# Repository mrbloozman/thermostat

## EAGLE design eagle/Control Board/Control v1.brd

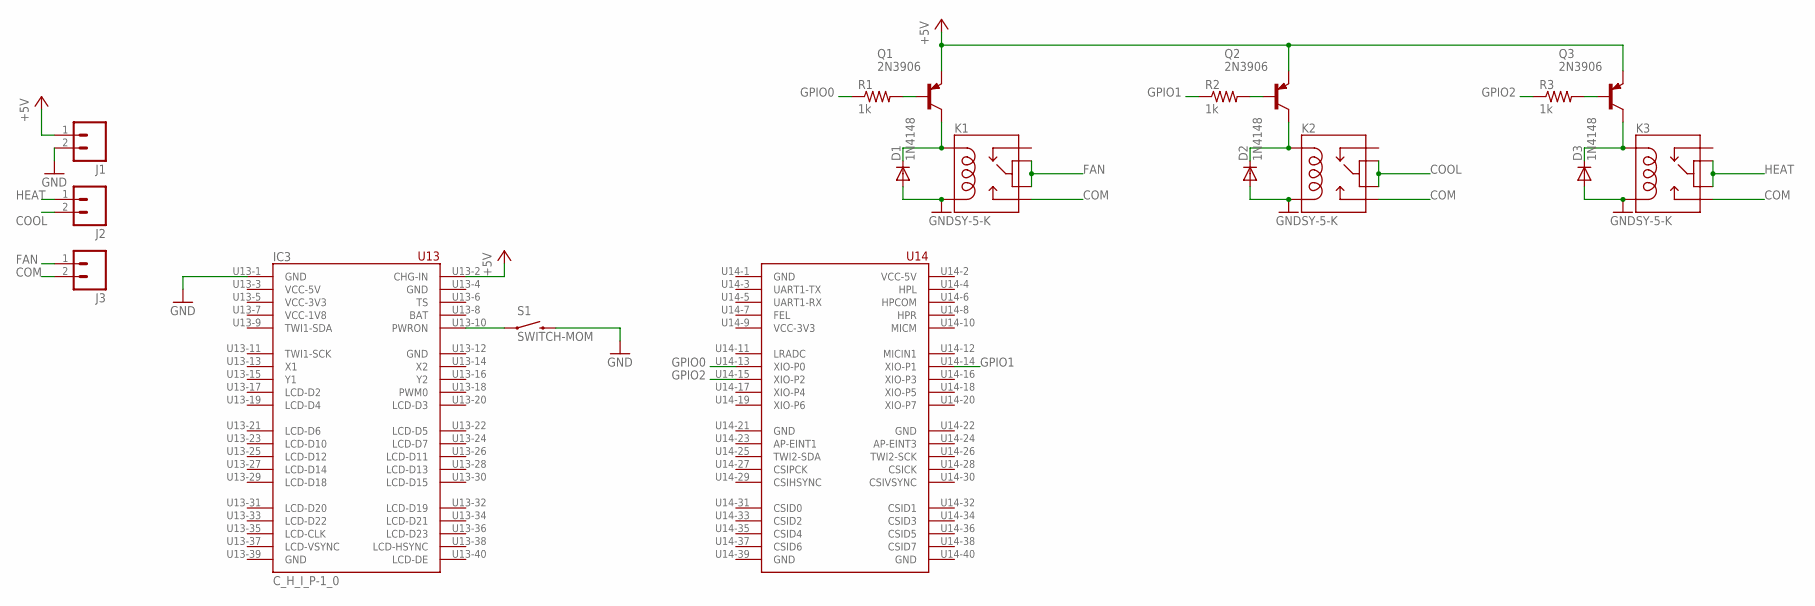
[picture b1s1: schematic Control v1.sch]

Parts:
D1, D2, D3: 1N4148; DO35-7
IC3: C_H_I_P-1_0
J1, J2, J3: M023.5MM; SCREWTERMINAL-3.5MM-2
K1, K2, K3: SY-5-K; RELAY-G5V
Q1, Q2, Q3: 2N3906; TO92
R1, R2, R3: 1k; 0207/10
S1: SWITCH-MOM; TACTILE-PTH

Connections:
+5V: IC3.U13-2 (CHG-IN), J1.1, Q1.3 (E), Q2.3 (E), Q3.3 (E)
BAT: IC3.U13-8 (BAT)
COM: J3.2, K1.10
COOL: J2.2, K2.5, K2.6
FAN: J3.1, K1.5, K1.6
GND: D1.A, D2.A, D3.A, IC3.U13-1 (GND), IC3.U13-4 (GND), IC3.U13-12 (GND), IC3.U13-39 (GND), IC3.U14-1 (GND), IC3.U14-21 (GND), IC3.U14-22 (GND), IC3.U14-39 (GND), IC3.U14-40 (GND), J1.2, K1.9, K2.9, K3.9, S1.3 (2)
GPIO0: IC3.U14-13 (XIO-P0), R1.1
GPIO1: IC3.U14-14 (XIO-P1), R2.1
GPIO2: IC3.U14-15 (XIO-P2), R3.1
HEAT: J2.1, K3.5, K3.6
unnamed: IC3.U13-10 (PWRON), S1.1
unnamed: Q2.2 (B), R2.2
unnamed: Q1.2 (B), R1.2
unnamed: D1.C, K1.2, Q1.1 (C)
unnamed: D2.C, K2.2, Q2.1 (C)
unnamed: Q3.2 (B), R3.2
unnamed: D3.C, K3.2, Q3.1 (C)

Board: 2 copper layers, 17 parts (1 on the bottom side), 16 nets, no tracks yet.

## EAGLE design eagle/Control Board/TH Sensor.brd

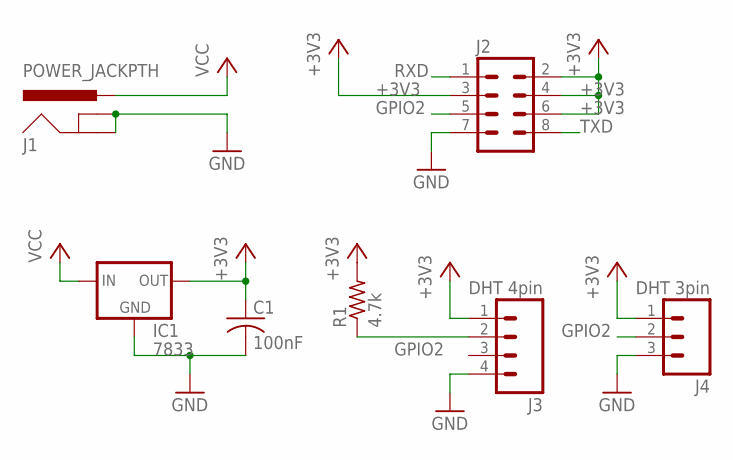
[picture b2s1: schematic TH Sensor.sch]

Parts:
C1: 100nF; C025-025X050
IC1: 7833; 78XXL
J1: POWER_JACKPTH; POWER_JACK_PTH
J2: M04X2; 2X4
J3: DHT 4pin; 1X04
J4: DHT 3pin; 1X03
R1: 4.7k; 0207/10

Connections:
+3V3: C1.1, IC1.OUT, J2.2, J2.3, J2.4, J2.6, J3.1, J4.1, R1.2
GND: C1.2, IC1.GND, J1.GND, J1.GNDBREAK, J2.7, J3.4, J4.3
GPIO2: J2.5, J3.2, J4.2, R1.1
RXD: J2.1
TXD: J2.8
VCC: IC1.IN, J1.PWR

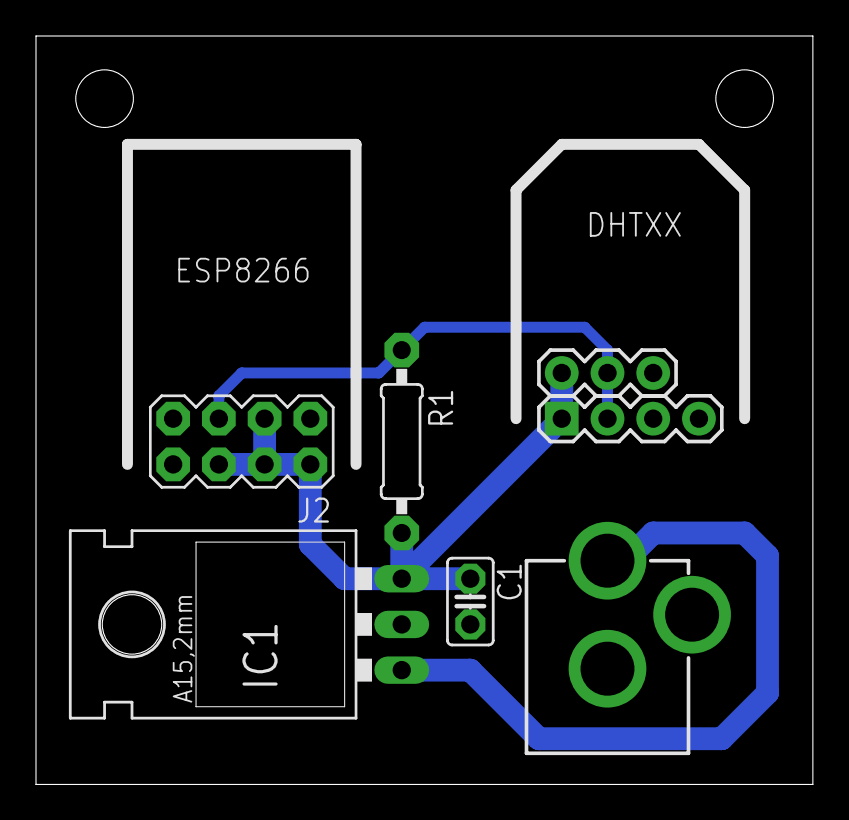
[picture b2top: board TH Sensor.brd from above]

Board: 2 copper layers, 43.2 x 41.6 mm, 7 parts (0 on the bottom side), 4 nets.

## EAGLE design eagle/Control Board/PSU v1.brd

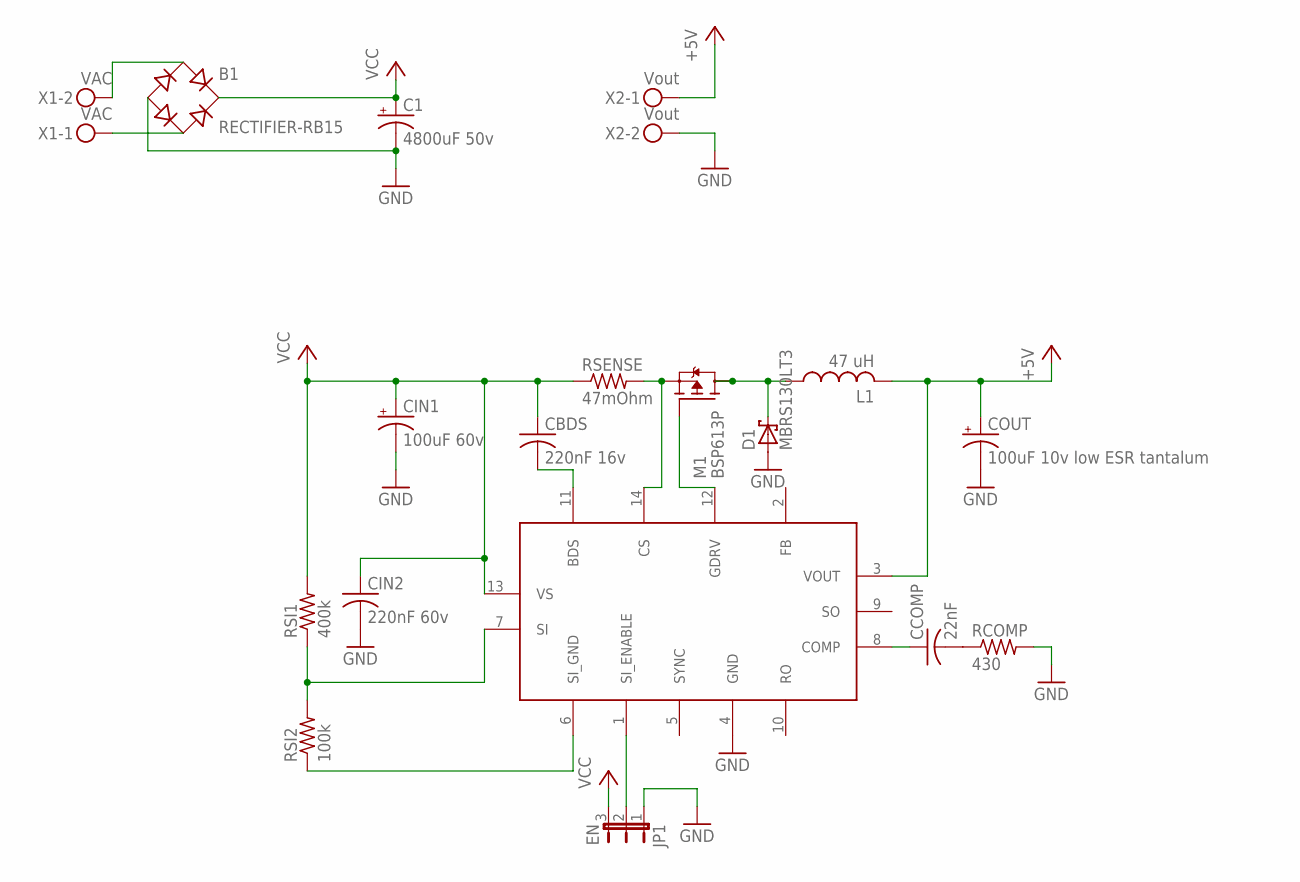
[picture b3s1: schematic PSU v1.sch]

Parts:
B1: RECTIFIER-RB15; RB15
C1: 4800uF 50v; E7,5-18
CBDS: 220nF 16v; C1206
CCOMP: 22nF; C1206
CIN1: 100uF 60v; 140CLH-1010
CIN2: 220nF 60v; C1206
COUT: 100uF 10v low ESR tantalum; D/7343-31R
D1: MBRS130LT3; SMB
IC1: IFX80471SKV50; PG-DSO-14
JP1: EN; JP2
L1: 47 uH; SRN6045TA
M1: BSP613P; PG-SOT-223
RCOMP: 430; R1206
RSENSE: 47mOhm; R2512
RSI1: 400k; R1206
RSI2: 100k; R1206
X1: VAC; MKDSN1,5/2-5,08
X2: Vout; MKDSN1,5/2-5,08

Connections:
+5V: COUT.+, IC1.3 (VOUT), L1.P$2 (2), X2.1
GND: B1.-, C1.-, CIN1.-, CIN2.2, COUT.-, D1.A, IC1.4 (GND), JP1.1, RCOMP.2, X2.2
unnamed: B1.AC1, X1.2
unnamed: B1.AC2, X1.1
unnamed: CBDS.2, IC1.11 (BDS)
unnamed: IC1.7 (SI), RSI1.1, RSI2.2
unnamed: IC1.6 (SI_GND), RSI2.1
unnamed: IC1.14 (CS), M1.3 (S), RSENSE.2
unnamed: CCOMP.2, RCOMP.1
unnamed: IC1.12 (GDRV), M1.1 (G)
unnamed: D1.C, L1.P$1 (1), M1.2 (D), M1.4 (D)
unnamed: CCOMP.1, IC1.8 (COMP)
unnamed: IC1.1 (SI_ENABLE), JP1.2
VCC: B1.+, C1.+, CBDS.1, CIN1.+, CIN2.1, IC1.13 (VS), JP1.3, RSENSE.1, RSI1.2

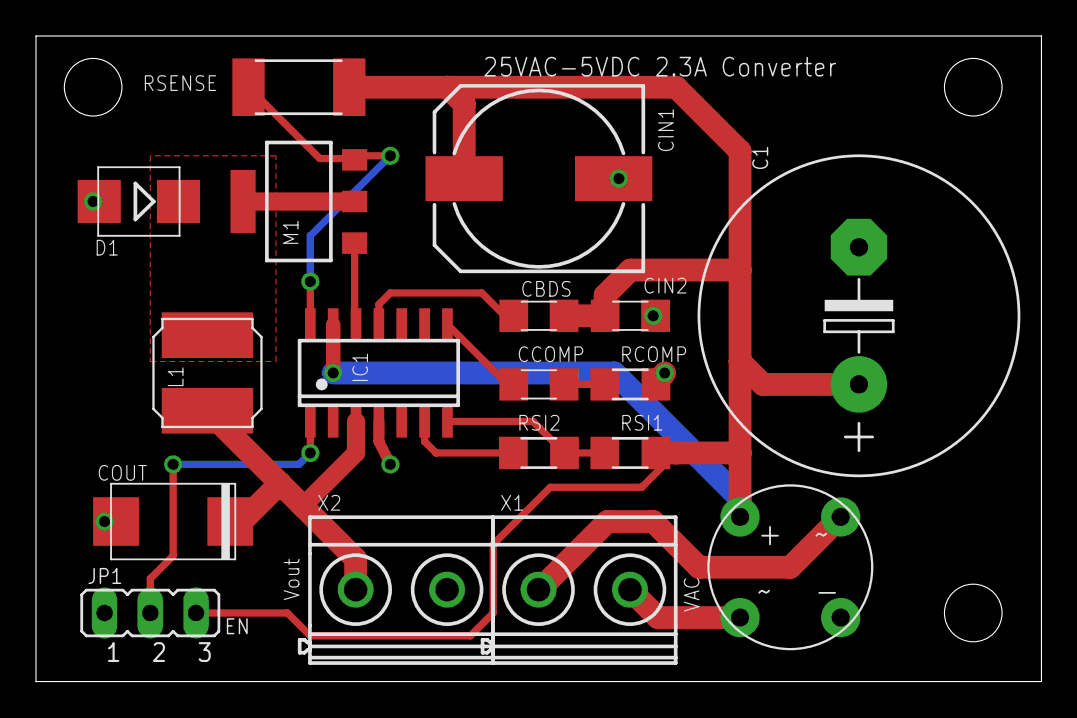
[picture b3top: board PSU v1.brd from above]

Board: 2 copper layers, 55.9 x 35.9 mm, 18 parts (0 on the bottom side), 14 nets.

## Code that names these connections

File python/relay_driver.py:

import CHIP_IO.GPIO as GPIO
import database

db = database.thermoDB('thermostat.db',debug=False)

class driver:
	def __init__(self):
		self.reset()

	def pinOn(self,p):
		# print 'pinOn('+p+')'
		GPIO.output(p,GPIO.LOW)

	def pinOff(self,p):
		# print 'pinOff('+p+')'
		GPIO.output(p,GPIO.HIGH)

	def reset(self):
		status = db.getSystemStatus()
		# print status
		self.heatPin=[e for e in status['relays'] if e['desc']=='Heat'][0]['pin']
		# print heatPin
		self.coolPin=[e for e in status['relays'] if e['desc']=='Cool'][0]['pin']
		# print coolPin
		self.fanPin=[e for e in status['relays'] if e['desc']=='Fan'][0]['pin']
		# print fanPin


		GPIO.cleanup()

		GPIO.setup(self.heatPin,GPIO.OUT)
		GPIO.setup(self.coolPin,GPIO.OUT)
		GPIO.setup(self.fanPin,GPIO.OUT)

		GPIO.output(self.heatPin,GPIO.HIGH)
		GPIO.output(self.coolPin,GPIO.HIGH)
		GPIO.output(self.fanPin,GPIO.HIGH)

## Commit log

2018-02-02 adding eagle dir
2018-02-02 menu button mapping
2018-02-03 renderButton
2018-02-03 button and menu classes
2018-02-03 Input, Button, and Spinbox classes
2018-02-03 debugging
2018-02-04 control class and kwargs
2018-02-04 Screen and ButtonGrid classes
2018-02-04 Control text placement
2018-02-04 Spinbox debugging, border
2018-02-04 Control formatting methods
2018-02-04 Control defaults and Grid class
2018-02-05 Toggle class
2018-02-05 Listbox class
2018-02-06 onTap onRender onChange
2018-02-06 spinbox and listbox enable - and event callback arg attr binding
2018-02-07 fix listbox rendering
2018-02-07 debugging enabled and added onSelect
2018-02-08 event callback adjustments and Control padding
2018-02-09 improving examples
2018-02-10 listbox example
2018-02-11 control parent inheritance
2018-02-13 listboxitem class
2018-02-14 Image class
2018-02-15 NetPBM class
2018-02-17 debugging image render
2018-02-18 Image render set active window and mem write
2018-02-18 more images in example
2018-02-18 image examples
2018-02-20 dynamic control example Clock class
2018-02-20 debugged Clock class
2018-02-20 mrbloozman_RA8875 and TouchDisplay class
2018-02-21 removing Adafruit ports
2018-02-22 cleanup

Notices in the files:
parts and their libraries:
SparkFun-Electromechanical: Licensing: Creative Commons ShareAlike 4.0 International - https://creativecommons.org/licenses/by-sa/4.0
